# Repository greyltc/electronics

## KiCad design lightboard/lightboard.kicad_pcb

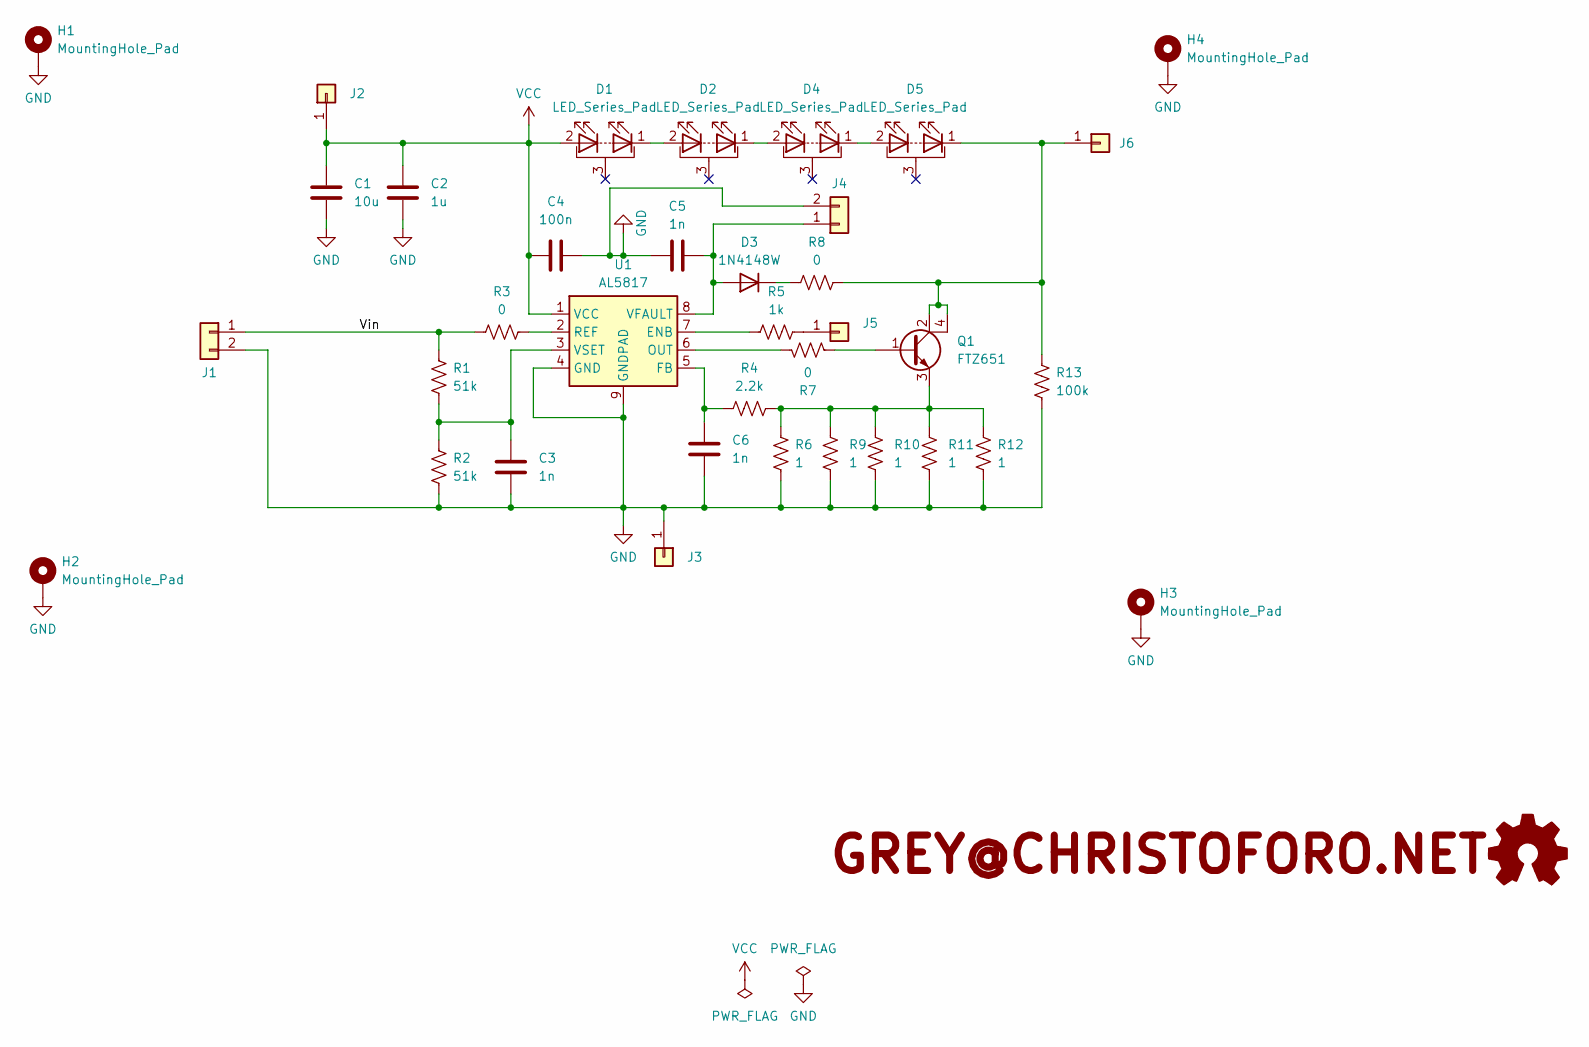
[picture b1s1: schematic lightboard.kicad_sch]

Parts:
C1: 10u; C_1210_3225Metric
C2: 1u; C_1206_3216Metric
C3, C5, C6: 1n; C_0603_1608Metric
C4: 100n; C_1206_3216Metric
D1, D2, D4, D5: LED_Series_Pad; LED_Osram_GH_FR4
D3: 1N4148W; D_SOD-123
H1, H2, H3, H4: MountingHole_Pad; MountingHole_4mm_Pad
J1, J4: Conn_01x02; BNC_TEConnectivity_1478035_Horizontal
J2, J3, J6: Conn_01x01; MountingHole_5.2mm_Pad
J5: Conn_01x01; TestPoint_Keystone_5010-5014_Multipurpose
Q1: FTZ651; SOT-223
R1, R2: 51k; R_0805_2012Metric
R3, R7, R8: 0; R_0805_2012Metric
R4: 2.2k; R_0805_2012Metric
R5: 1k; R_0805_2012Metric
R6, R9, R10, R11, R12: 1; R_1206_3216Metric
R13: 100k; R_0805_2012Metric
SYM1: logo
SYM2: Logo_Open_Hardware_Small; logo
U1: AL5817; MSOP-8-1EP_3x3mm_P0.65mm_EP1.73x1.85mm_ThermalVias

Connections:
/Vin: J1.1, R1.1, R3.1
GND: C1.2, C2.2, C3.2, C4.2, C5.1, C6.2, H1.1, H2.1, H3.1, H4.1, J1.2, J3.1, J4.2, R2.2, R6.2, R9.2, R10.2, R11.2, R12.2, R13.2, U1.4 (GND), U1.9 (GNDPAD)
unnamed: D1.1 (K), D2.2 (A)
unnamed: D2.1 (K), D4.2 (A)
unnamed: C5.2, D3.2 (A), J4.1, U1.8 (VFAULT)
unnamed: D3.1 (K), R8.1
unnamed: D4.1 (K), D5.2 (A)
unnamed: D5.1 (K), J6.1, Q1.2 (C), Q1.4 (C), R8.2, R13.1
unnamed: J5.1, R5.2
unnamed: Q1.1 (B), R7.1
unnamed: Q1.3 (E), R4.2, R6.1, R9.1, R10.1, R11.1, R12.1
unnamed: R5.1, U1.7 (ENB)
unnamed: C6.1, R4.1, U1.5 (FB)
unnamed: R7.2, U1.6 (OUT)
unnamed: R3.2, U1.2 (REF)
unnamed: C3.1, R1.2, R2.1, U1.3 (VSET)
VCC: C1.1, C2.1, C4.1, D1.2 (A), J2.1, U1.1 (VCC)

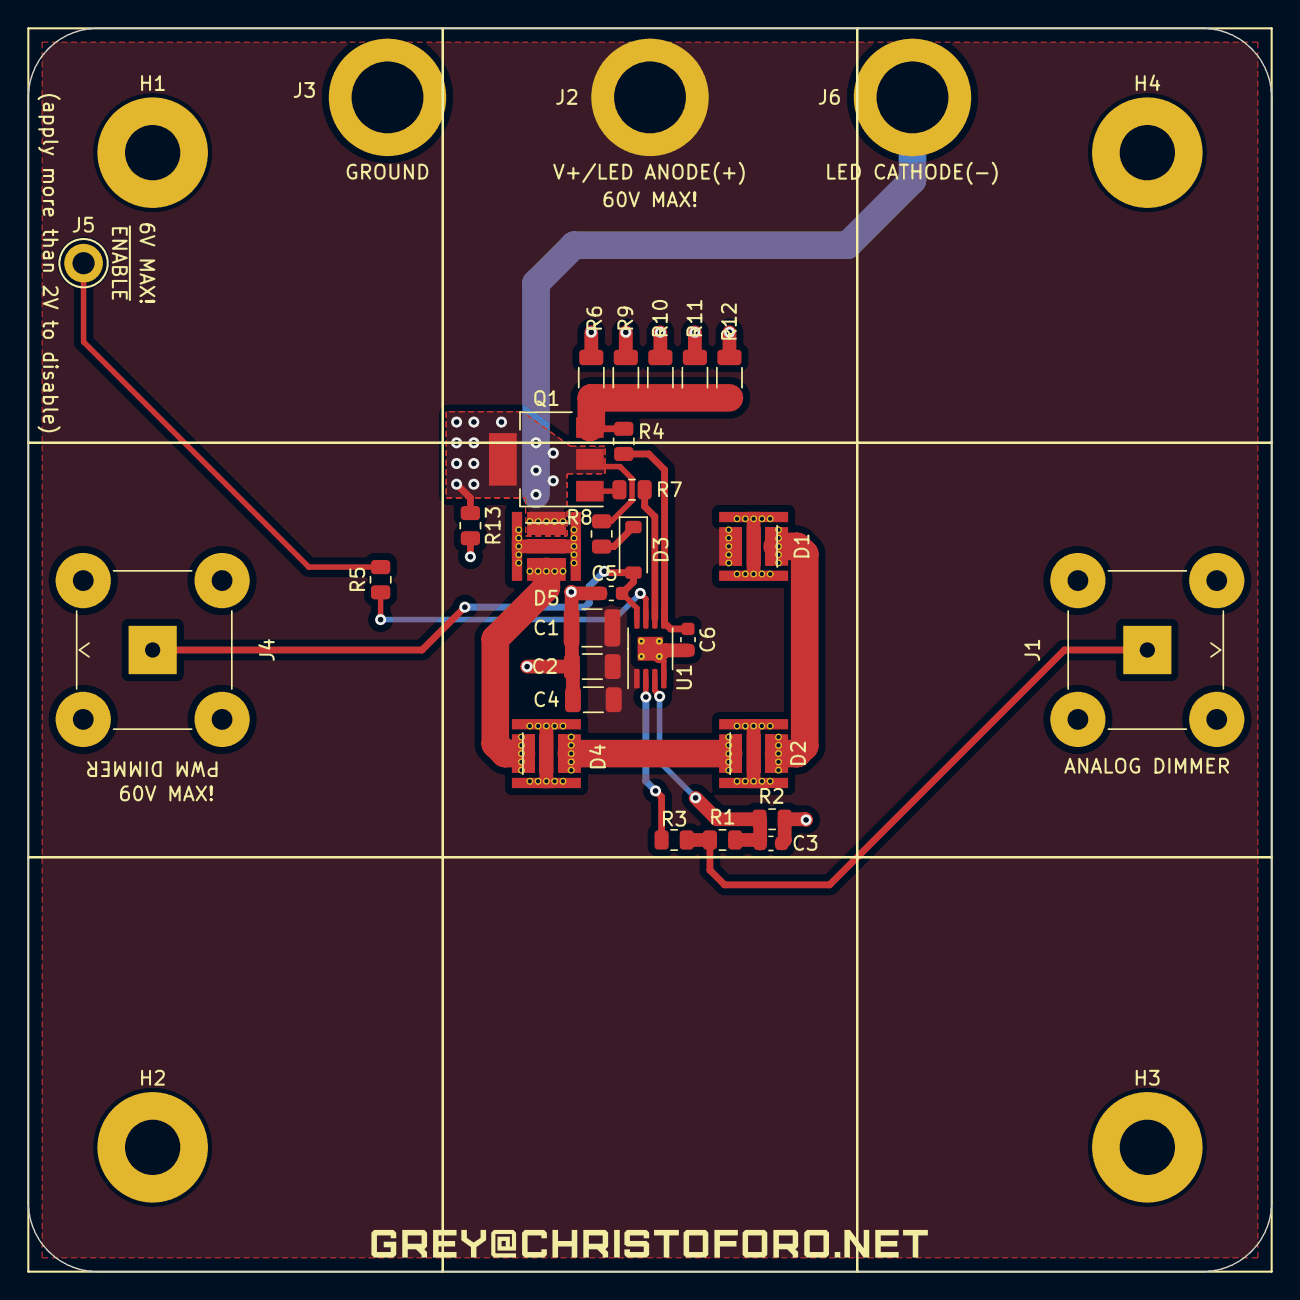
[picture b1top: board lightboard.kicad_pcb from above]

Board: 2 copper layers, 90.0 x 90.0 mm, 38 parts (1 on the bottom side), 17 nets.

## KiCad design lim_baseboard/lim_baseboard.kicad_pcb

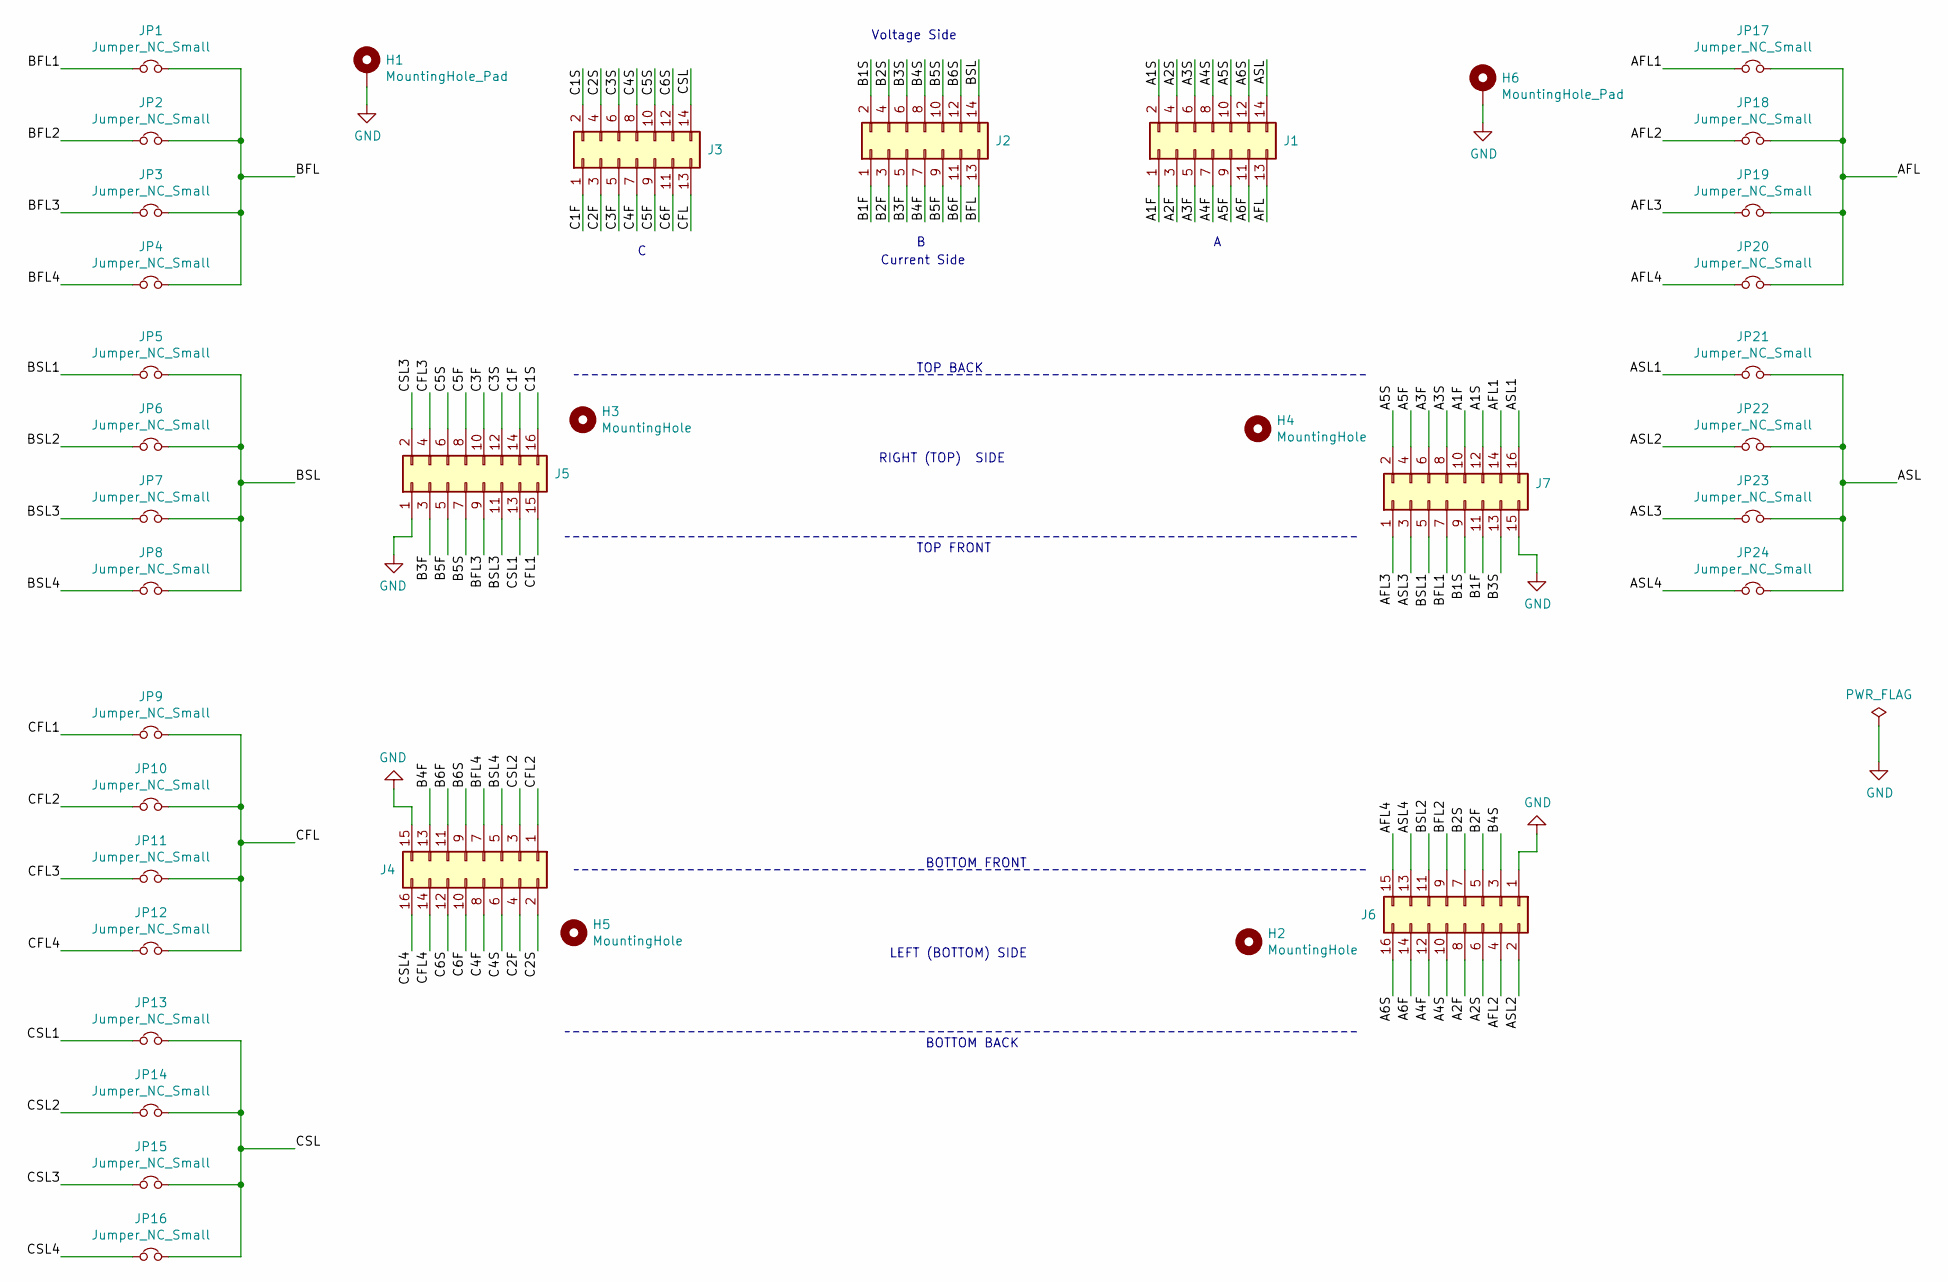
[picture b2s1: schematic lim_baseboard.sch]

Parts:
H1, H6: MountingHole_Pad; MountingHole_4.3mm_M4_Pad_Via
H2, H3, H4, H5: MountingHole; MountingHole_4.3mm_M4
J1, J2, J3: Conn_02x07_Odd_Even; IDC-Header_2x07_P2.54mm_Vertical
J4, J5, J6, J7: Conn_02x08_Odd_Even; Samtec_MECF-08-01-NP-L-DV-WT_2x08_P1.27mm_Socket_Horizontal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
JP1, JP2, JP3, JP4, JP5, JP6, JP7, JP8, JP9, JP10, JP11, JP12, JP13, JP14, JP15, JP16, JP17, JP18, JP19, JP20, JP21, JP22, JP23, JP24: Jumper_NC_Small; SolderJumper-2_P1.3mm_Bridged_RoundedPad1.0x1.5mm

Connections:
/A1F: J1.1, J7.10
/A1S: J1.2, J7.12
/A2F: J1.3, J6.8
/A2S: J1.4, J6.6
/A3F: J1.5, J7.6
/A3S: J1.6, J7.8
/A4F: J1.7, J6.12
/A4S: J1.8, J6.10
/A5F: J1.9, J7.4
/A5S: J1.10, J7.2
/A6F: J1.11, J6.14
/A6S: J1.12, J6.16
/AFL: J1.13, JP17.2, JP18.2, JP19.2, JP20.2
/AFL1: J7.14, JP17.1
/AFL2: J6.4, JP18.1
/AFL3: J7.1, JP19.1
/AFL4: J6.15, JP20.1
/ASL: J1.14, JP21.2, JP22.2, JP23.2, JP24.2
/ASL1: J7.16, JP21.1
/ASL2: J6.2, JP22.1
/ASL3: J7.3, JP23.1
/ASL4: J6.13, JP24.1
/B1F: J2.1, J7.11
/B1S: J2.2, J7.9
/B2F: J2.3, J6.5
/B2S: J2.4, J6.7
/B3F: J2.5, J5.3
/B3S: J2.6, J7.13
/B4F: J2.7, J4.13
/B4S: J2.8, J6.3
/B5F: J2.9, J5.5
/B5S: J2.10, J5.7
/B6F: J2.11, J4.11
/B6S: J2.12, J4.9
/BFL: J2.13, JP1.2, JP2.2, JP3.2, JP4.2
/BFL1: J7.7, JP1.1
/BFL2: J6.9, JP2.1
/BFL3: J5.9, JP3.1
/BFL4: J4.7, JP4.1
/BSL: J2.14, JP5.2, JP6.2, JP7.2, JP8.2
/BSL1: J7.5, JP5.1
/BSL2: J6.11, JP6.1
/BSL3: J5.11, JP7.1
/BSL4: J4.5, JP8.1
/C1F: J3.1, J5.14
/C1S: J3.2, J5.16
/C2F: J3.3, J4.4
/C2S: J3.4, J4.2
/C3F: J3.5, J5.10
/C3S: J3.6, J5.12
/C4F: J3.7, J4.8
/C4S: J3.8, J4.6
/C5F: J3.9, J5.8
/C5S: J3.10, J5.6
/C6F: J3.11, J4.10
/C6S: J3.12, J4.12
/CFL: J3.13, JP9.2, JP10.2, JP11.2, JP12.2
/CFL1: J5.15, JP9.1
/CFL2: J4.1, JP10.1
/CFL3: J5.4, JP11.1
/CFL4: J4.14, JP12.1
/CSL: J3.14, JP13.2, JP14.2, JP15.2, JP16.2
/CSL1: J5.13, JP13.1
/CSL2: J4.3, JP14.1
/CSL3: J5.2, JP15.1
/CSL4: J4.16, JP16.1
GND: H1.1, H6.1, J4.15, J5.1, J6.1, J7.15

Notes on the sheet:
Current Side
Voltage Side
LEFT (BOTTOM) SIDE
RIGHT (TOP) SIDE
BOTTOM BACK
BOTTOM FRONT
TOP FRONT
TOP BACK

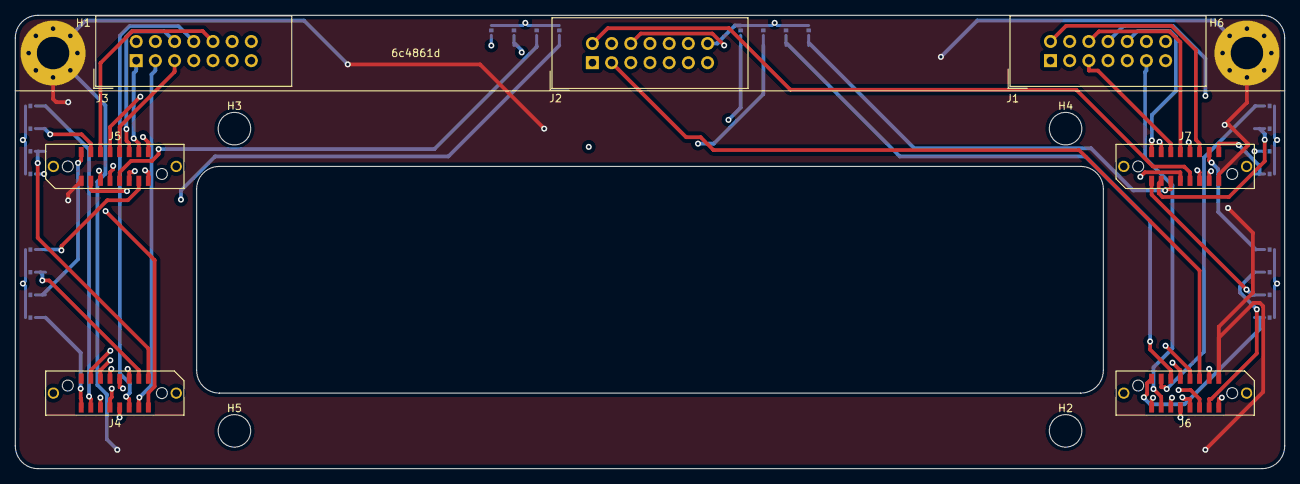
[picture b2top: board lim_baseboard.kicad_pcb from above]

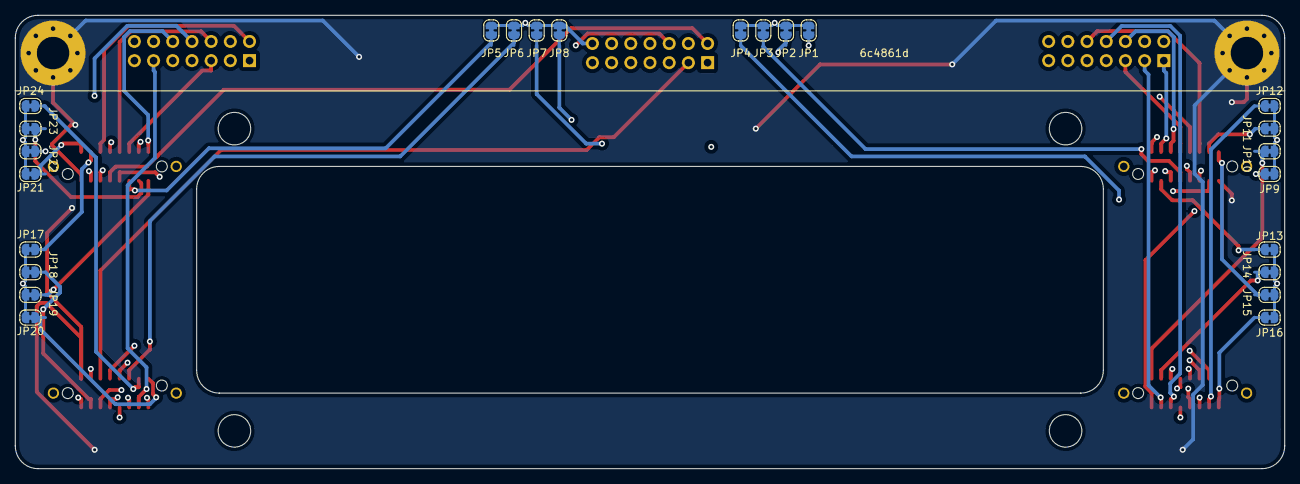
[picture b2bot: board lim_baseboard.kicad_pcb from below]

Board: 4 copper layers, 168.0 x 60.0 mm, 37 parts (24 on the bottom side), 67 nets.

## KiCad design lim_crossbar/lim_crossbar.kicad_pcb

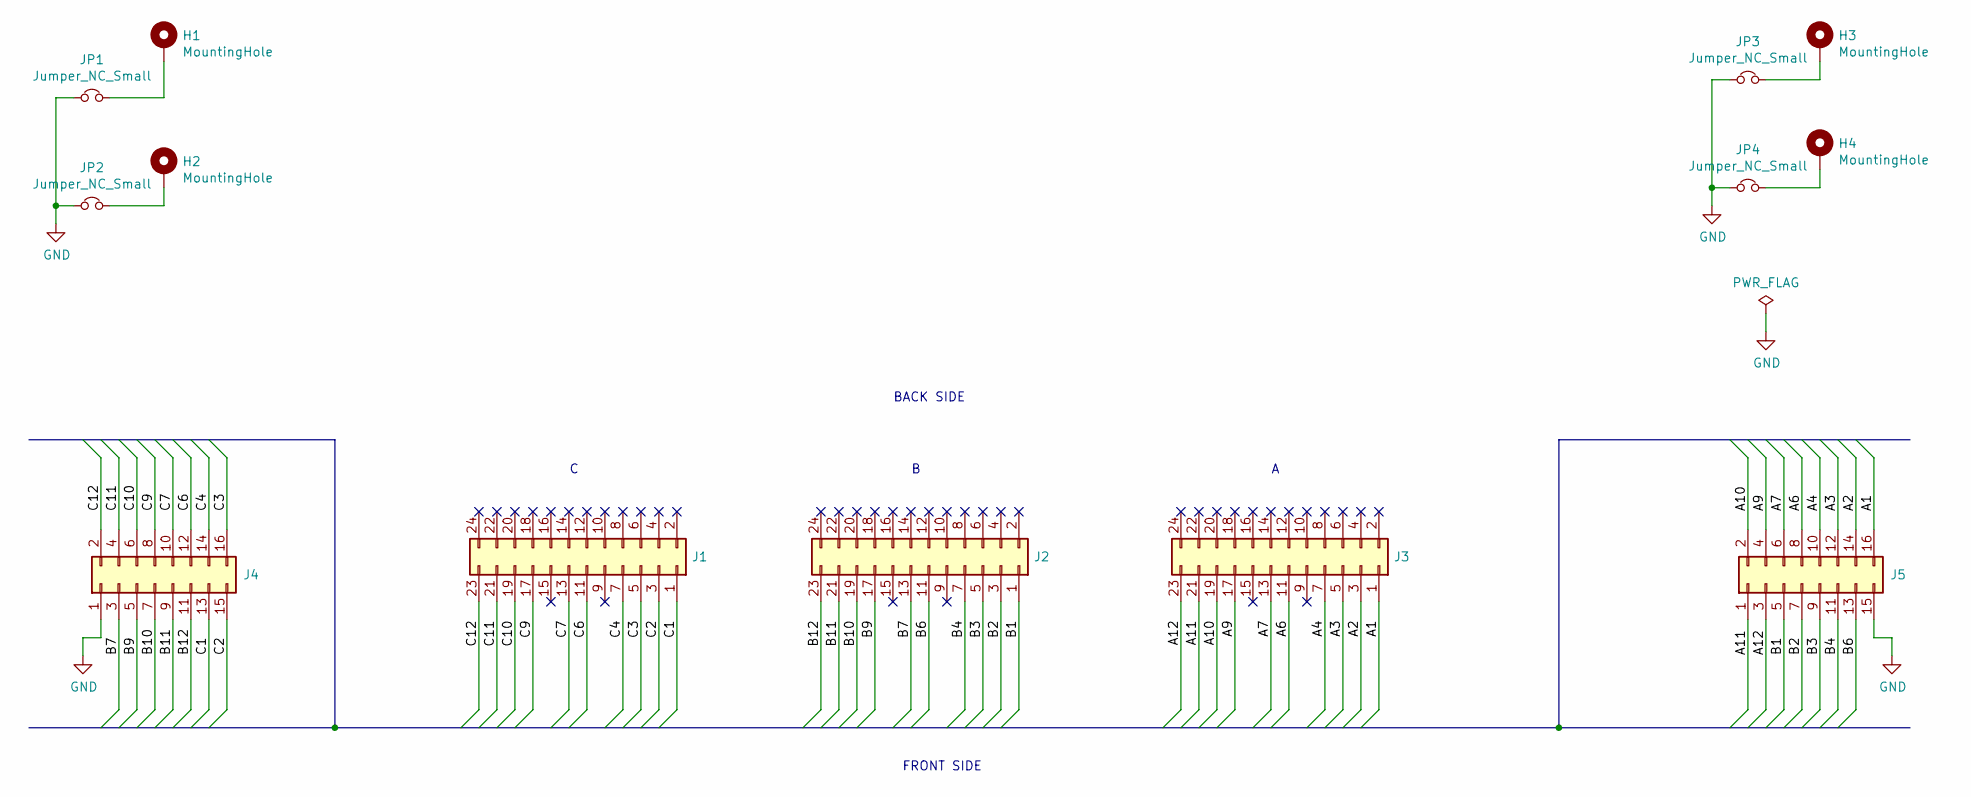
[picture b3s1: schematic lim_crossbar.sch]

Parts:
H1, H2, H3, H4: MountingHole; MountingHole_2.2mm_M2_Pad_Via
J1, J2, J3: Conn_02x12_Counter_Clockwise; PinSocket_2x12_P2.00mm_Vertical_EDGE; mfg_part SQT-112-03-F-D
J4, J5: Conn_02x08_Odd_Even; Samtec_MECF-08-0_-NP-L-DV_2x08_P1.27mm_Edge_mod; mfg_part MECF-08-01-L-DV-NP-WT
JP1, JP2, JP3, JP4: Jumper_NC_Small; SolderJumper-2_P1.3mm_Bridged_RoundedPad1.0x1.5mm

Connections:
/A1: J3.1, J5.16
/A2: J3.3, J5.14
/A3: J3.5, J5.12
/A4: J3.7, J5.10
/A6: J3.11, J5.8
/A7: J3.13, J5.6
/A9: J3.17, J5.4
/A10: J3.19, J5.2
/A11: J3.21, J5.1
/A12: J3.23, J5.3
/B1: J2.1, J5.5
/B2: J2.3, J5.7
/B3: J2.5, J5.9
/B4: J2.7, J5.11
/B6: J2.11, J5.13
/B7: J2.13, J4.3
/B9: J2.17, J4.5
/B10: J2.19, J4.7
/B11: J2.21, J4.9
/B12: J2.23, J4.11
/C1: J1.1, J4.13
/C2: J1.3, J4.15
/C3: J1.5, J4.16
/C4: J1.7, J4.14
/C6: J1.11, J4.12
/C7: J1.13, J4.10
/C9: J1.17, J4.8
/C10: J1.19, J4.6
/C11: J1.21, J4.4
/C12: J1.23, J4.2
GND: J4.1, J5.15, JP1.1, JP2.1, JP3.1, JP4.1
unnamed: H1.1, JP1.2
unnamed: H2.1, JP2.2
unnamed: H3.1, JP3.2
unnamed: H4.1, JP4.2

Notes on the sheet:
FRONT SIDE
BACK SIDE

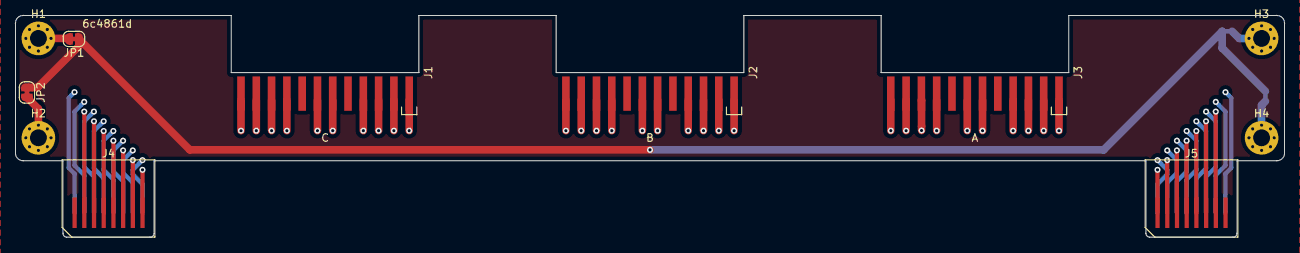
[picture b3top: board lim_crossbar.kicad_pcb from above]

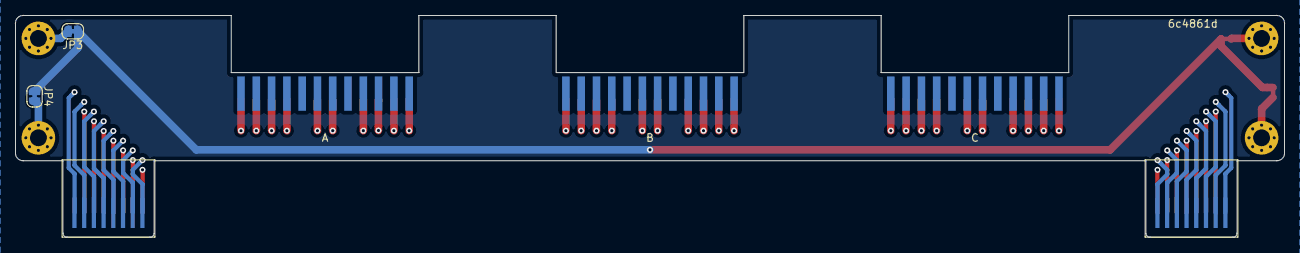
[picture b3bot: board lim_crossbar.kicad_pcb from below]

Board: 4 copper layers, 166.0 x 29.0 mm, 13 parts (2 on the bottom side), 35 nets.

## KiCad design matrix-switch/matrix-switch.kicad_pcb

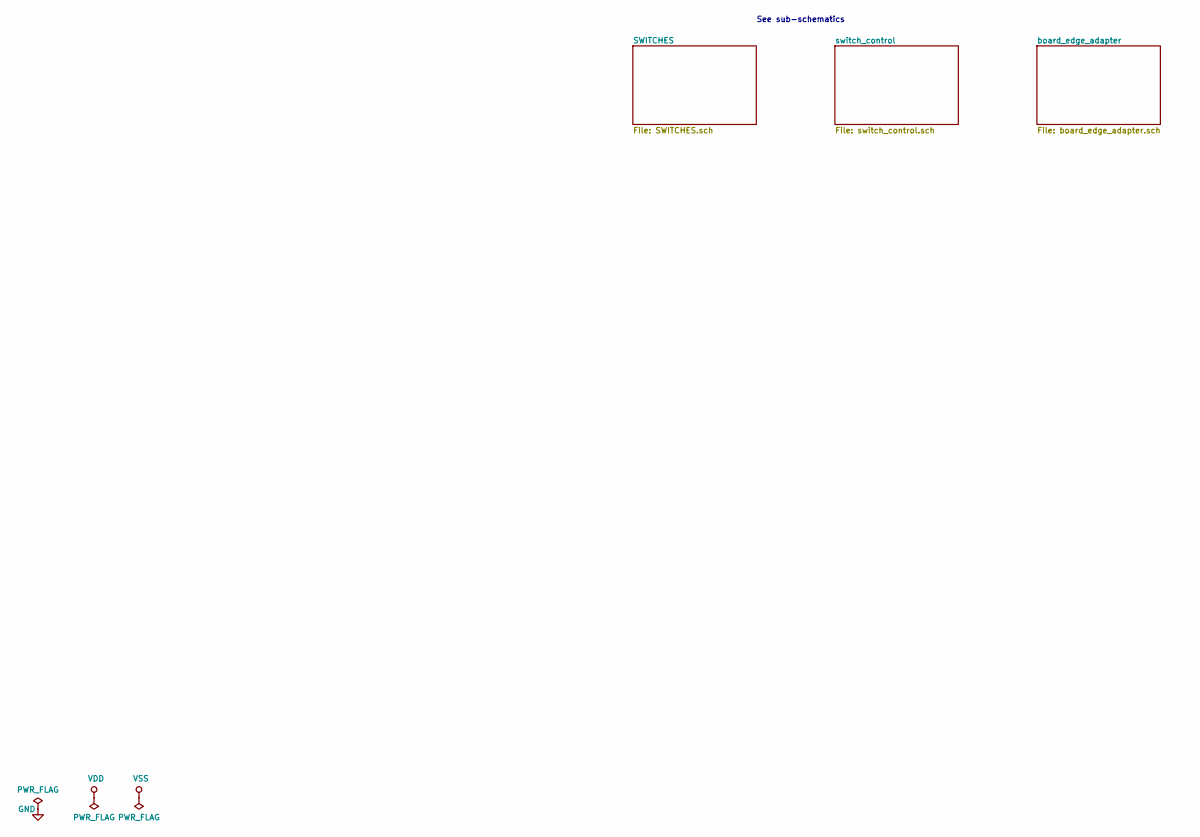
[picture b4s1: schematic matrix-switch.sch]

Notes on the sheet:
See sub-schematics

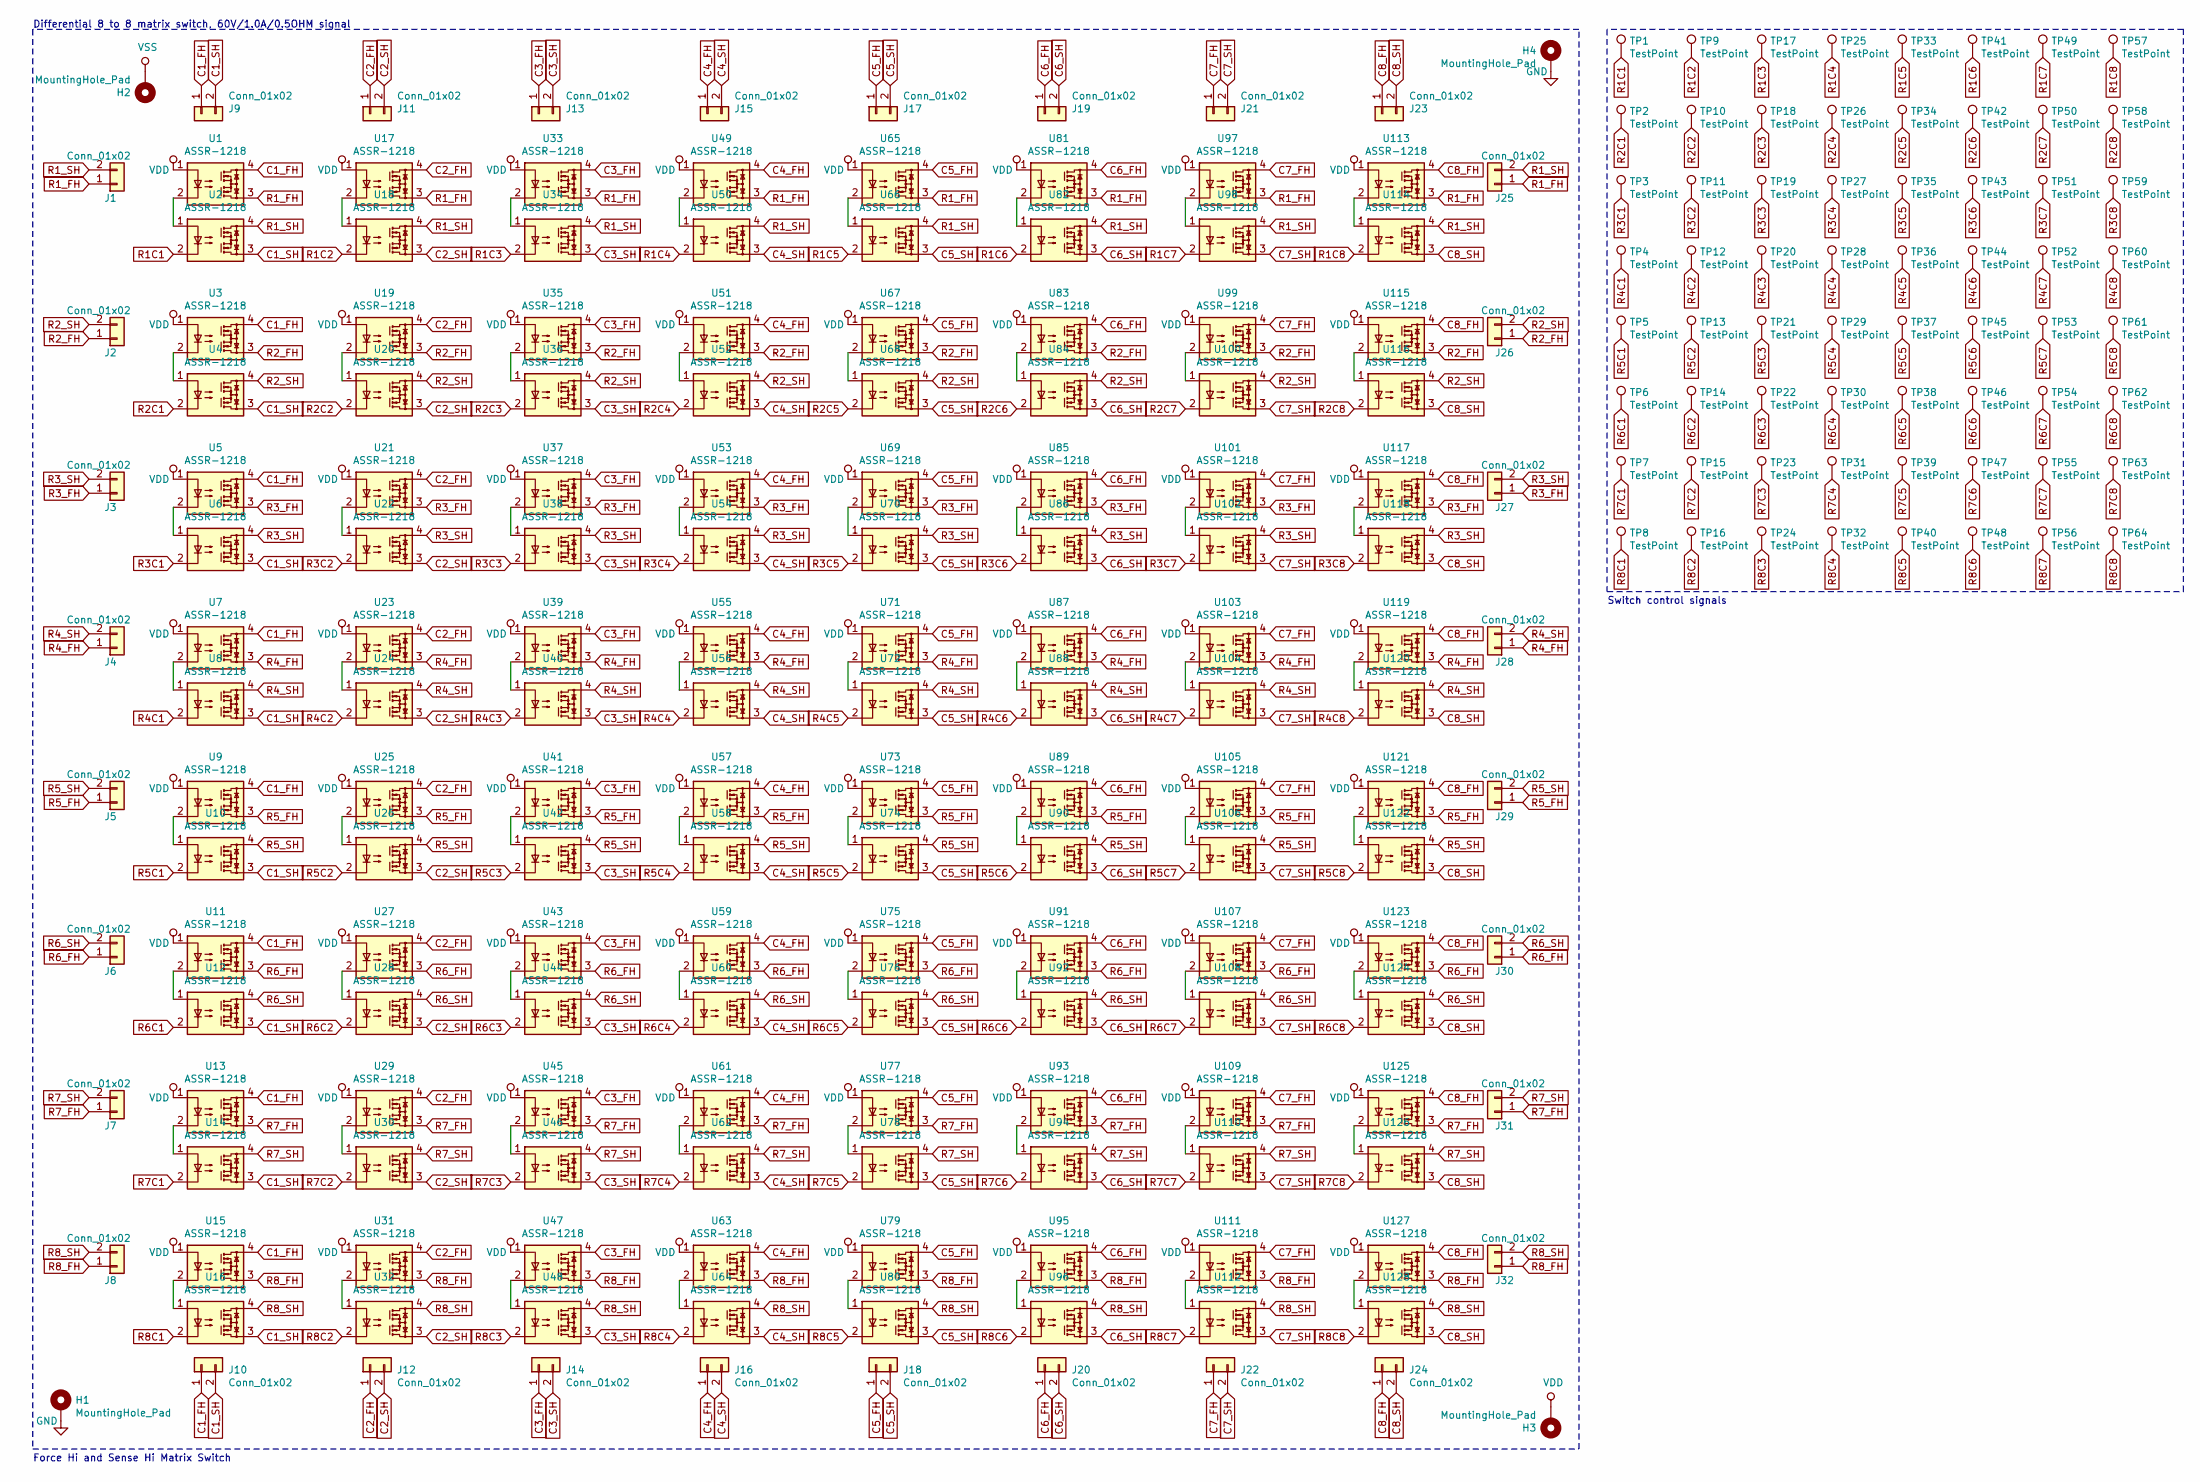
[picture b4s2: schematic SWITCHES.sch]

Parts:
H1, H2, H3, H4: MountingHole_Pad; MountingHole_2.2mm_M2_Pad_Via
J1, J2, J3, J4, J5, J6, J7, J8, J9, J10, J11, J12, J13, J14, J15, J16, J17, J18, J19, J20, J21, J22, J23, J24, J25, J26, J27, J28, J29, J30, J31, J32: Conn_01x02; PinHeader_1x02_P2.54mm_Vertical
TP1, TP2, TP3, TP4, TP5, TP6, TP7, TP8, TP9, TP10, TP11, TP12, TP13, TP14, TP15, TP16, TP17, TP18, TP19, TP20, TP21, TP22, TP23, TP24, TP25, TP26, TP27, TP28, TP29, TP30, TP31, TP32, TP33, TP34, TP35, TP36, TP37, TP38, TP39, TP40, TP41, TP42, TP43, TP44, TP45, TP46, TP47, TP48, TP49, TP50, TP51, TP52, TP53, TP54, TP55, TP56, TP57, TP58, TP59, TP60, TP61, TP62, TP63, TP64: TestPoint; TestPoint_Pad_D1.0mm
U1, U2, U3, U4, U5, U6, U7, U8, U9, U10, U11, U12, U13, U14, U15, U16, U17, U18, U19, U20, U21, U22, U23, U24, U25, U26, U27, U28, U29, U30, U31, U32, U33, U34, U35, U36, U37, U38, U39, U40, U41, U42, U43, U44, U45, U46, U47, U48, U49, U50, U51, U52, U53, U54, U55, U56, U57, U58, U59, U60, U61, U62, U63, U64, U65, U66, U67, U68, U69, U70, U71, U72, U73, U74, U75, U76, U77, U78, U79, U80, U81, U82, U83, U84, U85, U86, U87, U88, U89, U90, U91, U92, U93, U94, U95, U96, U97, U98, U99, U100, U101, U102, U103, U104, U105, U106, U107, U108, U109, U110, U111, U112, U113, U114, U115, U116, U117, U118, U119, U120, U121, U122, U123, U124, U125, U126, U127, U128: ASSR-1218; SO-4_4.4x4.3mm_P2.54mm

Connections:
C1_FH: J9.1, J10.1, U1.4, U3.4, U5.4, U7.4, U9.4, U11.4, U13.4, U15.4; also elsewhere on the board
C1_SH: J9.2, J10.2, U2.3, U4.3, U6.3, U8.3, U10.3, U12.3, U14.3, U16.3; also elsewhere on the board
C2_FH: J11.1, J12.1, U17.4, U19.4, U21.4, U23.4, U25.4, U27.4, U29.4, U31.4; also elsewhere on the board
C2_SH: J11.2, J12.2, U18.3, U20.3, U22.3, U24.3, U26.3, U28.3, U30.3, U32.3; also elsewhere on the board
C3_FH: J13.1, J14.1, U33.4, U35.4, U37.4, U39.4, U41.4, U43.4, U45.4, U47.4; also elsewhere on the board
C3_SH: J13.2, J14.2, U34.3, U36.3, U38.3, U40.3, U42.3, U44.3, U46.3, U48.3; also elsewhere on the board
C4_FH: J15.1, J16.1, U49.4, U51.4, U53.4, U55.4, U57.4, U59.4, U61.4, U63.4; also elsewhere on the board
C4_SH: J15.2, J16.2, U50.3, U52.3, U54.3, U56.3, U58.3, U60.3, U62.3, U64.3; also elsewhere on the board
C5_FH: J17.1, J18.1, U65.4, U67.4, U69.4, U71.4, U73.4, U75.4, U77.4, U79.4; also elsewhere on the board
C5_SH: J17.2, J18.2, U66.3, U68.3, U70.3, U72.3, U74.3, U76.3, U78.3, U80.3; also elsewhere on the board
C6_FH: J19.1, J20.1, U81.4, U83.4, U85.4, U87.4, U89.4, U91.4, U93.4, U95.4; also elsewhere on the board
C6_SH: J19.2, J20.2, U82.3, U84.3, U86.3, U88.3, U90.3, U92.3, U94.3, U96.3; also elsewhere on the board
C7_FH: J21.1, J22.1, U97.4, U99.4, U101.4, U103.4, U105.4, U107.4, U109.4, U111.4; also elsewhere on the board
C7_SH: J21.2, J22.2, U98.3, U100.3, U102.3, U104.3, U106.3, U108.3, U110.3, U112.3; also elsewhere on the board
C8_FH: J23.1, J24.1, U113.4, U115.4, U117.4, U119.4, U121.4, U123.4, U125.4, U127.4; also elsewhere on the board
C8_SH: J23.2, J24.2, U114.3, U116.3, U118.3, U120.3, U122.3, U124.3, U126.3, U128.3; also elsewhere on the board
GND: H1.1, H4.1; also elsewhere on the board
unnamed: U1.2, U2.1
unnamed: U3.2, U4.1
unnamed: U5.2, U6.1
unnamed: U7.2, U8.1
unnamed: U9.2, U10.1
unnamed: U11.2, U12.1
unnamed: U13.2, U14.1
unnamed: U15.2, U16.1
unnamed: U17.2, U18.1
unnamed: U19.2, U20.1
unnamed: U21.2, U22.1
unnamed: U23.2, U24.1
unnamed: U25.2, U26.1
unnamed: U27.2, U28.1
unnamed: U29.2, U30.1
unnamed: U31.2, U32.1
unnamed: U33.2, U34.1
unnamed: U35.2, U36.1
unnamed: U37.2, U38.1
unnamed: U39.2, U40.1
unnamed: U41.2, U42.1
unnamed: U43.2, U44.1
unnamed: U45.2, U46.1
unnamed: U47.2, U48.1
unnamed: U49.2, U50.1
unnamed: U51.2, U52.1
unnamed: U53.2, U54.1
unnamed: U55.2, U56.1
unnamed: U57.2, U58.1
unnamed: U59.2, U60.1
unnamed: U61.2, U62.1
unnamed: U63.2, U64.1
unnamed: U65.2, U66.1
unnamed: U67.2, U68.1
unnamed: U69.2, U70.1
unnamed: U71.2, U72.1
unnamed: U73.2, U74.1
unnamed: U75.2, U76.1
unnamed: U77.2, U78.1
unnamed: U79.2, U80.1
unnamed: U81.2, U82.1
unnamed: U83.2, U84.1
unnamed: U85.2, U86.1
unnamed: U87.2, U88.1
unnamed: U89.2, U90.1
unnamed: U91.2, U92.1
unnamed: U93.2, U94.1
unnamed: U95.2, U96.1
unnamed: U97.2, U98.1
unnamed: U99.2, U100.1
unnamed: U101.2, U102.1
unnamed: U103.2, U104.1
unnamed: U105.2, U106.1
unnamed: U107.2, U108.1
unnamed: U109.2, U110.1
unnamed: U111.2, U112.1
unnamed: U113.2, U114.1
unnamed: U115.2, U116.1
unnamed: U117.2, U118.1
unnamed: U119.2, U120.1
unnamed: U121.2, U122.1
unnamed: U123.2, U124.1
unnamed: U125.2, U126.1
unnamed: U127.2, U128.1
R1C1: TP1.1, U2.2
R1C2: TP9.1, U18.2
R1C3: TP17.1, U34.2
R1C4: TP25.1, U50.2
R1C5: TP33.1, U66.2
R1C6: TP41.1, U82.2
R1C7: TP49.1, U98.2
R1C8: TP57.1, U114.2
R1_FH: J1.1, J25.1, U1.3, U17.3, U33.3, U49.3, U65.3, U81.3, U97.3, U113.3; also elsewhere on the board
R1_SH: J1.2, J25.2, U2.4, U18.4, U34.4, U50.4, U66.4, U82.4, U98.4, U114.4; also elsewhere on the board
R2C1: TP2.1, U4.2
R2C2: TP10.1, U20.2
R2C3: TP18.1, U36.2
R2C4: TP26.1, U52.2
R2C5: TP34.1, U68.2
R2C6: TP42.1, U84.2
R2C7: TP50.1, U100.2
R2C8: TP58.1, U116.2
R2_FH: J2.1, J26.1, U3.3, U19.3, U35.3, U51.3, U67.3, U83.3, U99.3, U115.3; also elsewhere on the board
R2_SH: J2.2, J26.2, U4.4, U20.4, U36.4, U52.4, U68.4, U84.4, U100.4, U116.4; also elsewhere on the board
R3C1: TP3.1, U6.2
R3C2: TP11.1, U22.2
R3C3: TP19.1, U38.2
R3C4: TP27.1, U54.2
R3C5: TP35.1, U70.2
R3C6: TP43.1, U86.2
R3C7: TP51.1, U102.2
R3C8: TP59.1, U118.2
R3_FH: J3.1, J27.1, U5.3, U21.3, U37.3, U53.3, U69.3, U85.3, U101.3, U117.3; also elsewhere on the board
R3_SH: J3.2, J27.2, U6.4, U22.4, U38.4, U54.4, U70.4, U86.4, U102.4, U118.4; also elsewhere on the board
R4C1: TP4.1, U8.2
R4C2: TP12.1, U24.2
R4C3: TP20.1, U40.2
R4C4: TP28.1, U56.2
R4C5: TP36.1, U72.2
R4C6: TP44.1, U88.2
R4C7: TP52.1, U104.2
R4C8: TP60.1, U120.2
R4_FH: J4.1, J28.1, U7.3, U23.3, U39.3, U55.3, U71.3, U87.3, U103.3, U119.3; also elsewhere on the board
R4_SH: J4.2, J28.2, U8.4, U24.4, U40.4, U56.4, U72.4, U88.4, U104.4, U120.4; also elsewhere on the board
R5C1: TP5.1, U10.2
R5C2: TP13.1, U26.2
R5C3: TP21.1, U42.2
R5C4: TP29.1, U58.2
R5C5: TP37.1, U74.2
R5C6: TP45.1, U90.2
R5C7: TP53.1, U106.2
R5C8: TP61.1, U122.2
R5_FH: J5.1, J29.1, U9.3, U25.3, U41.3, U57.3, U73.3, U89.3, U105.3, U121.3; also elsewhere on the board
R5_SH: J5.2, J29.2, U10.4, U26.4, U42.4, U58.4, U74.4, U90.4, U106.4, U122.4; also elsewhere on the board
R6C1: TP6.1, U12.2
R6C2: TP14.1, U28.2
R6C3: TP22.1, U44.2
R6C4: TP30.1, U60.2
R6C5: TP38.1, U76.2
R6C6: TP46.1, U92.2
R6C7: TP54.1, U108.2
R6C8: TP62.1, U124.2
R6_FH: J6.1, J30.1, U11.3, U27.3, U43.3, U59.3, U75.3, U91.3, U107.3, U123.3; also elsewhere on the board
R6_SH: J6.2, J30.2, U12.4, U28.4, U44.4, U60.4, U76.4, U92.4, U108.4, U124.4; also elsewhere on the board
R7C1: TP7.1, U14.2
R7C2: TP15.1, U30.2
R7C3: TP23.1, U46.2
R7C4: TP31.1, U62.2
R7C5: TP39.1, U78.2
R7C6: TP47.1, U94.2
R7C7: TP55.1, U110.2
R7C8: TP63.1, U126.2
R7_FH: J7.1, J31.1, U13.3, U29.3, U45.3, U61.3, U77.3, U93.3, U109.3, U125.3; also elsewhere on the board
R7_SH: J7.2, J31.2, U14.4, U30.4, U46.4, U62.4, U78.4, U94.4, U110.4, U126.4; also elsewhere on the board
R8C1: TP8.1, U16.2
R8C2: TP16.1, U32.2
R8C3: TP24.1, U48.2
R8C4: TP32.1, U64.2
R8C5: TP40.1, U80.2
R8C6: TP48.1, U96.2
R8C7: TP56.1, U112.2
R8C8: TP64.1, U128.2
R8_FH: J8.1, J32.1, U15.3, U31.3, U47.3, U63.3, U79.3, U95.3, U111.3, U127.3; also elsewhere on the board
R8_SH: J8.2, J32.2, U16.4, U32.4, U48.4, U64.4, U80.4, U96.4, U112.4, U128.4; also elsewhere on the board
VDD: H3.1, U1.1, U3.1, U5.1, U7.1, U9.1, U11.1, U13.1, U15.1, U17.1, U19.1, U21.1, U23.1, U25.1, U27.1, U29.1, U31.1, U33.1, U35.1, U37.1, U39.1, U41.1, U43.1, U45.1, U47.1, U49.1, U51.1, U53.1, U55.1, U57.1, U59.1, U61.1, U63.1, U65.1, U67.1, U69.1, U71.1, U73.1, U75.1, U77.1, U79.1, U81.1, U83.1, U85.1, U87.1, U89.1, U91.1, U93.1, U95.1, U97.1, U99.1, U101.1, U103.1, U105.1, U107.1, U109.1, U111.1, U113.1, U115.1, U117.1, U119.1, U121.1, U123.1, U125.1, U127.1; also elsewhere on the board
VSS: H2.1; also elsewhere on the board

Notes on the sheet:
Differential 8 to 8 matrix switch, 60V/1.0A/0.5OHM signal
Force Hi and Sense Hi Matrix Switch
Switch control signals
